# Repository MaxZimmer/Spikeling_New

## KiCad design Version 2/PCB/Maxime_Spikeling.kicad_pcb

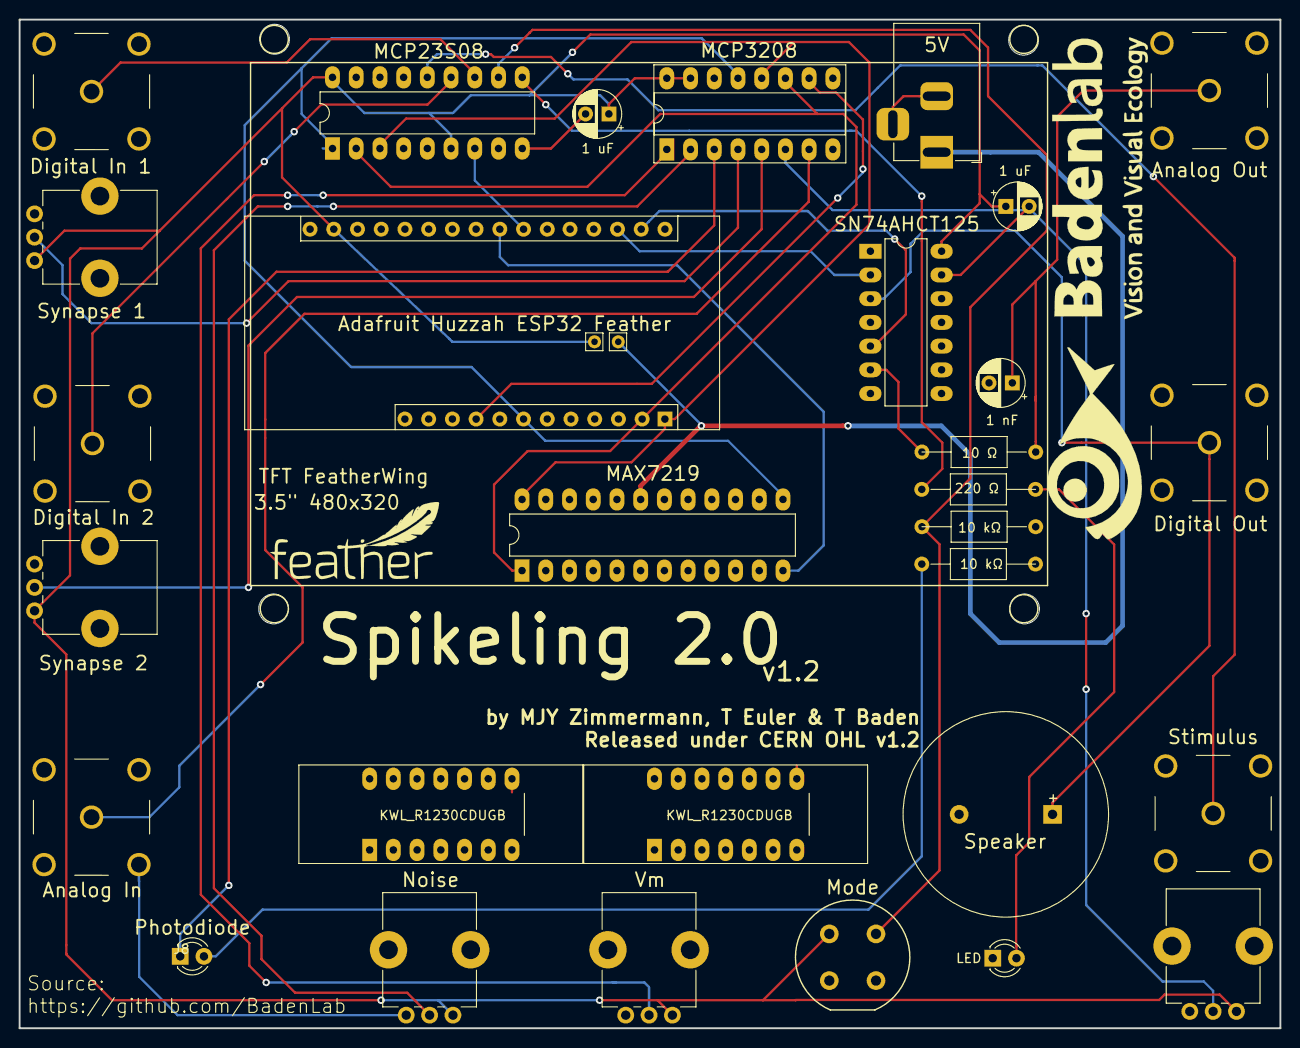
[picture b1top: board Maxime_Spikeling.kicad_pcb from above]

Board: 2 copper layers, 135.0 x 108.0 mm, 19 parts (0 on the bottom side), 5 nets.

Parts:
1 nF, 1 uF, 1 uF#2: CP_Radial_D5.0mm_P2.50mm
5V: BarrelJack_Horizontal
10 kΩ, 10 Ω: R_Axial_DIN0309_L9.0mm_D3.2mm_P15.24mm_Horizontal
Analog In: BNC connector
Analog Out: BNC connector
Digital In 1, Digital In 2: BNC connector
Digital Out: BNC connector
J8: Photodiode; LED_D3.0mm
LED: LED_D3.0mm
Mode: Push_E-Switch_KS01Q01
Speaker: Buzzer_15x7.5RM7.6
Stimulus: BNC connector
Synapse 1, Synapse 2: Potentiometer_Alps_RK09K_Single_Vertical
Vm: Potentiometer_Alps_RK09K_Single_Vertical

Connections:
GNDREF: 1 nF.2, 1 uF#2.2, 5V.2, 5V.3, 10 kΩ.1, Analog In.2, Analog Out.2, Digital In 1.2, Digital In 2.2, Digital Out.2, LED.1, Speaker.2, Stimulus.2, Synapse 1.3, Synapse 2.3, Vm.3
unnamed: Digital Out.1, Speaker.1
unnamed: 1 uF.1, 1 uF#2.1, Mode.1, Synapse 1.1, Synapse 2.1, Vm.1
unnamed: 1 nF.1, 10 Ω.1, Analog Out.1
unnamed: 10 kΩ.2, Mode.2

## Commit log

2019-02-11 version 2

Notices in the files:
Version 2/PCB/Maxime_Spikeling.kicad_pcb:
Released under CERN OHL v1.2
